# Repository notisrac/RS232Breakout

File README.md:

# RS232 breakout board

Simple breakout board for the 9 pin D-sub ([DE-9](https://en.wikipedia.org/wiki/D-subminiature#DE-9)) [RS-232](https://en.wikipedia.org/wiki/RS-232) connector.

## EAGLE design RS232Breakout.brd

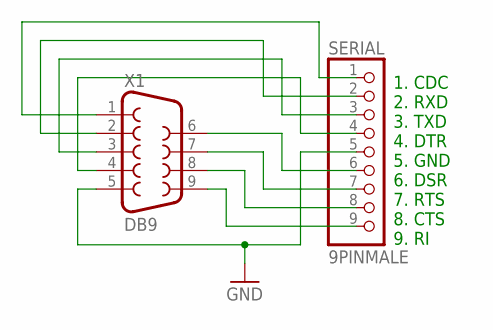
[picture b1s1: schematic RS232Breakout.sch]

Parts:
SERIAL: 9PINMALE; 1X09
X1: DB9; F09HP

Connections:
GND: SERIAL.5, X1.5
unnamed: SERIAL.9, X1.9
unnamed: SERIAL.8, X1.8
unnamed: SERIAL.7, X1.7
unnamed: SERIAL.6, X1.6
unnamed: SERIAL.4, X1.4
unnamed: SERIAL.3, X1.3
unnamed: SERIAL.2, X1.2
unnamed: SERIAL.1, X1.1

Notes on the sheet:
1. CDC 2. RXD 3. TXD 4. DTR 5. GND 6. DSR 7. RTS 8. CTS 9. RI

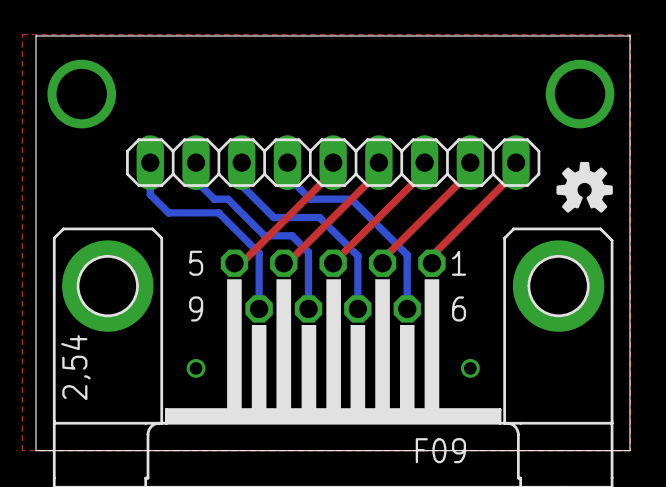
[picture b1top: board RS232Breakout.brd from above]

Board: 2 copper layers, 33.0 x 23.0 mm, 3 parts (0 on the bottom side), 9 nets.

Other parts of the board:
U$4: OSHW-LOGO-S

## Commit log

2018-07-27 Fixed README issues
2018-07-28 Added GA beacon to the README
2018-07-29 Added gitattributes
2018-07-29 Removed epf file

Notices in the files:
parts and their libraries:
SparkFun-Aesthetics: Licensing: Creative Commons ShareAlike 4.0 International - https://creativecommons.org/licenses/by-sa/4.0
